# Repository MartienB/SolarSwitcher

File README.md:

The goal of the SolarSwitcher project is to develop a device which can switch between differen power supplies in order to (in this case) power a Raspberry Pi. One of the connected power suppies is a small solar panel and battery, the goal is to use this power source as much as possible, but when the battery runs low, a wallcharger will take over.

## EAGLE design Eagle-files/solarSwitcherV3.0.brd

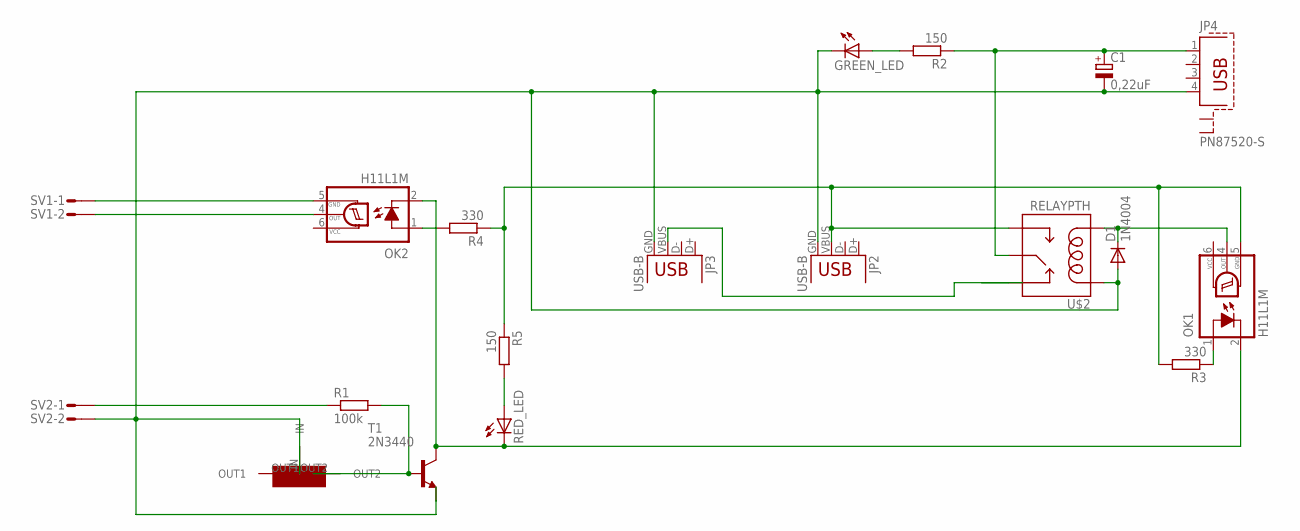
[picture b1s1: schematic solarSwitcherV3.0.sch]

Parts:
C1: 0,22uF; 150CLZ-1014
D1: 1N4004; DO41-10
GREEN_LED: LED5MM
JP2, JP3: USB-B; USB-B-PTH
JP4: PN87520-S
OK1, OK2: H11L1M; DIL06
R1: 100k; 0207/10
R2, R5: 150; 0207/10
R3, R4: 330; 0207/10
RED_LED: LED5MM
SV1, SV2: L02P
T1: 2N3440; TO5
U$2: RELAYPTH; SRD-05VDC-SL-C
U$5: 20k; POT_TRIMMER

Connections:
unnamed: R1.2, T1.2 (B), U$5.OUT2
unnamed: OK2.1 (A), R4.2
unnamed: OK2.4 (OUT), SV1.2
unnamed: R1.1, SV2.1
unnamed: JP3.VBUS, U$2.SWCLOSED (SWCLOSE)
unnamed: OK2.5 (GND), SV1.1
unnamed: C1.+, JP4.1, R2.1, U$2.SWCOMMON
unnamed: OK1.2 (C), OK2.2 (C), RED_LED.K (C), T1.3 (C)
unnamed: JP2.VBUS, OK1.5 (GND), R3.2, R4.1, R5.1, U$2.SWOPEN
unnamed: GREEN_LED.A, R2.2
unnamed: R5.2, RED_LED.A
unnamed: C1.-, D1.A, GREEN_LED.K (C), JP2.GND, JP3.GND, JP4.4, SV2.2, T1.1 (E), U$2.COIL1, U$5.IN
unnamed: D1.C, OK1.4 (OUT), U$2.COIL0
unnamed: OK1.1 (A), R3.1
VCC: OK1.6 (VCC), OK2.6 (VCC)

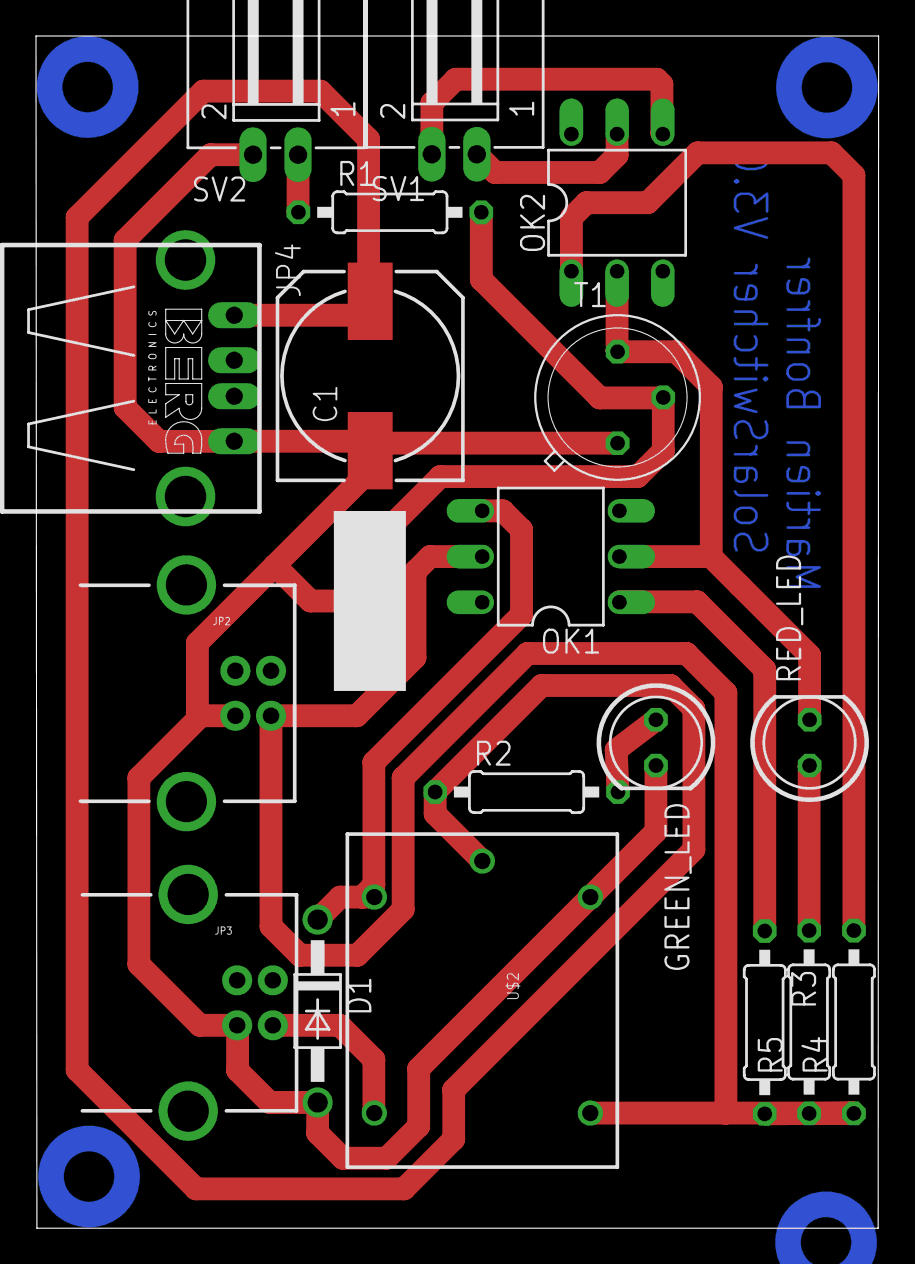
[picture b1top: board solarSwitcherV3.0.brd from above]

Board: 2 copper layers, 46.8 x 66.2 mm, 19 parts (0 on the bottom side), 15 nets.

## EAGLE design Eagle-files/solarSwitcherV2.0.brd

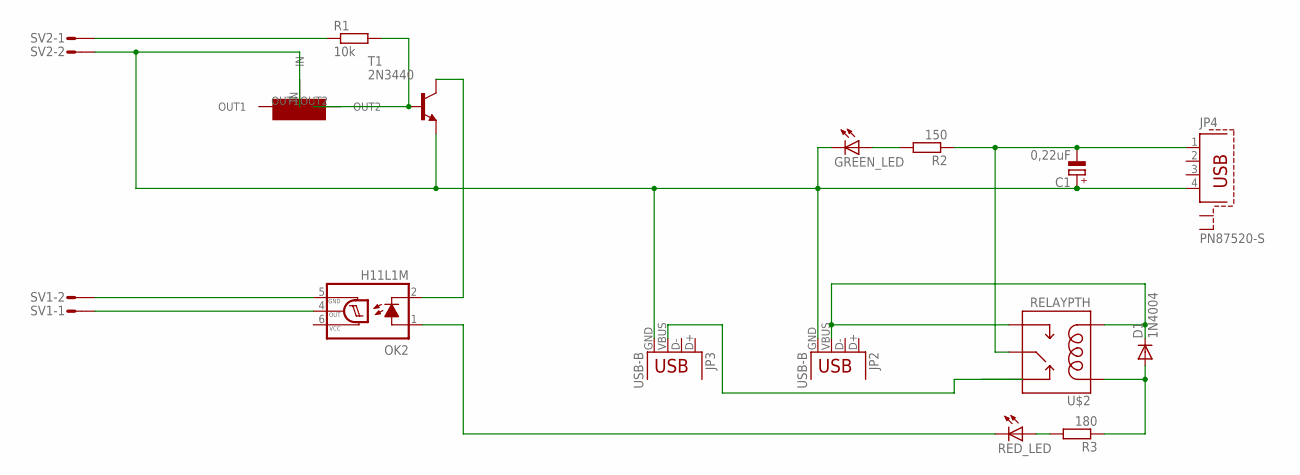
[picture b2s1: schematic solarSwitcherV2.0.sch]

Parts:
C1: 0,22uF; 150CLZ-1014
D1: 1N4004; DO41-10
GREEN_LED: LED5MM
JP2, JP3: USB-B; USB-B-PTH
JP4: PN87520-S
OK2: H11L1M; DIL06
R1: 10k; 0207/10
R2: 150; 0207/10
R3: 180; 0207/10
RED_LED: LED5MM
SV1, SV2: L02P
T1: 2N3440; TO5
U$2: RELAYPTH; SRD-05VDC-SL-C
U$5: 20k; POT_TRIMMER

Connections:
unnamed: R1.2, T1.2 (B), U$5.OUT2
unnamed: C1.-, JP4.1, R2.1, U$2.SWCOMMON
unnamed: OK2.1 (A), RED_LED.K (C)
unnamed: OK2.4 (OUT), SV1.1
unnamed: R1.1, SV2.1
unnamed: JP3.VBUS, U$2.SWCLOSED (SWCLOSE)
unnamed: OK2.5 (GND), SV1.2
unnamed: C1.+, GREEN_LED.K (C), JP2.GND, JP3.GND, JP4.4, SV2.2, T1.1 (E), U$5.IN
unnamed: OK2.2 (C), T1.3 (C)
unnamed: D1.A, R3.1, U$2.COIL1
unnamed: D1.C, JP2.VBUS, U$2.COIL0, U$2.SWOPEN
unnamed: GREEN_LED.A, R2.2
unnamed: R3.2, RED_LED.A
VCC: OK2.6 (VCC)

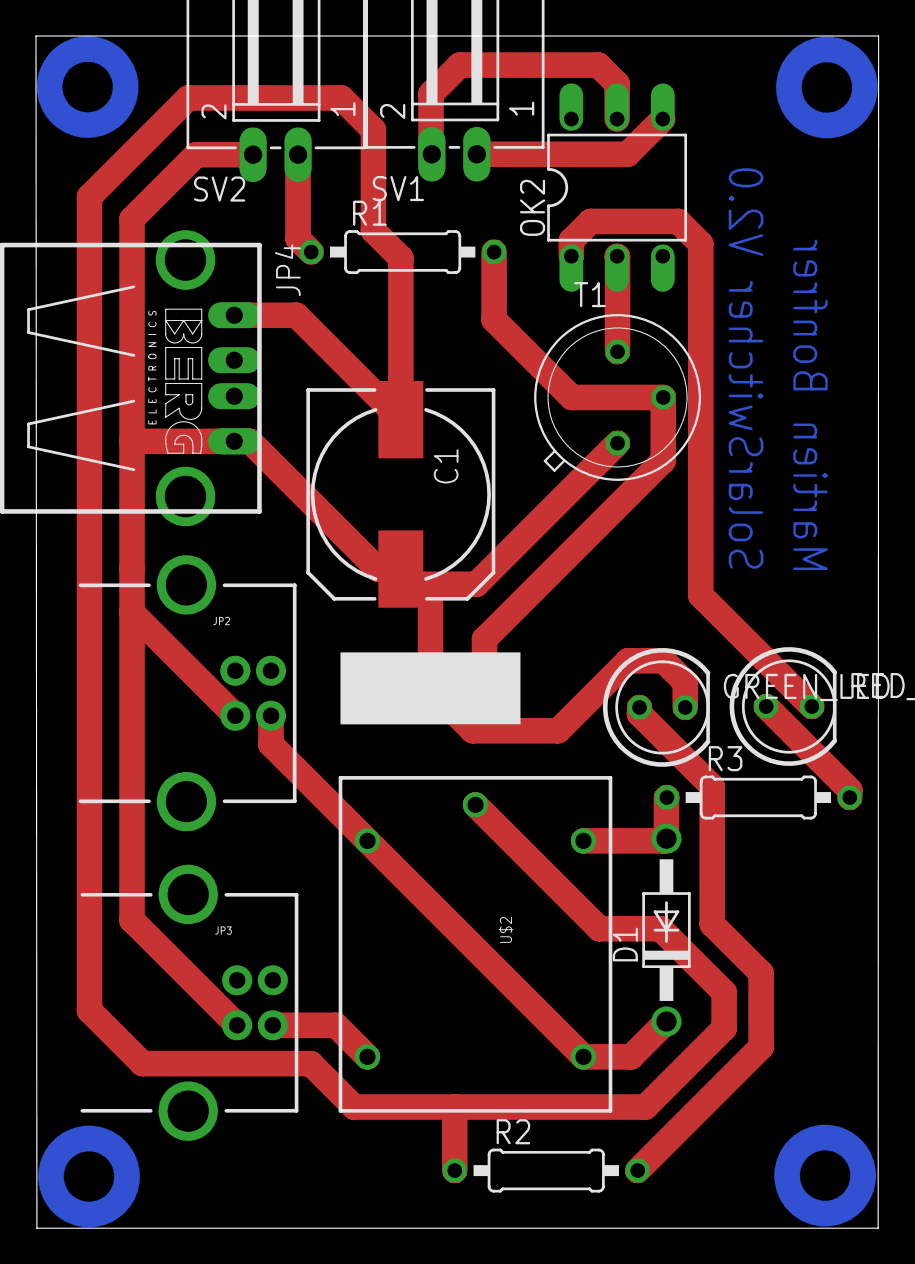
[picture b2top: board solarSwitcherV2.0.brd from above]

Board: 2 copper layers, 46.8 x 66.2 mm, 16 parts (0 on the bottom side), 13 nets.

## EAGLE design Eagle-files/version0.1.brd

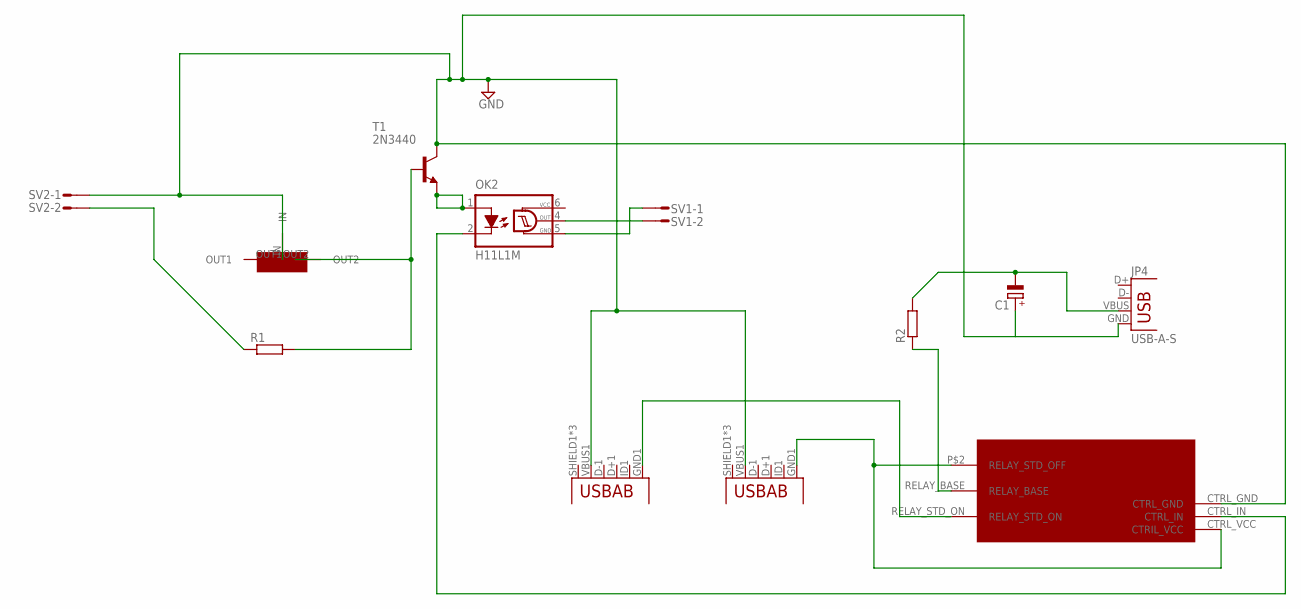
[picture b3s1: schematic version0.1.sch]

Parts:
C1: CPOL-EU150CLZ-1014; 150CLZ-1014
JP2, JP3: USB-ABCONN-11794; USB-AB-MICRO-SMD_V03
JP4: USB-A-S
OK2: H11L1M; DIL06
R1, R2: R-EU_VMTB60; VMTB60
SV1, SV2: L02P
T1: 2N3440; TO5
U$1: RELAY_BOARD
U$5: POT_TRIMMER

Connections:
GND: C1.+, JP2.VBUS1 (VBUS), JP3.VBUS1 (VBUS), JP4.GND, SV2.1, T1.3 (C), U$1.CTRL_GND, U$5.IN
unnamed: R1.2, T1.2 (B), U$5.OUT2
unnamed: C1.-, JP4.VBUS, R2.2
unnamed: OK2.2 (C), U$1.CTRL_IN
unnamed: JP2.GND1 (GND), U$1.CTRL_VCC (CTRIL_VCC), U$1.P$2 (RELAY_STD_OFF)
unnamed: R1.1, SV2.2
unnamed: JP3.GND1 (GND), U$1.RELAY_STD_ON
unnamed: OK2.5 (GND), SV1.1
unnamed: OK2.1 (A), T1.1 (E)
unnamed: OK2.4 (OUT), SV1.2
unnamed: R2.1, U$1.RELAY_BASE
VCC: OK2.6 (VCC)

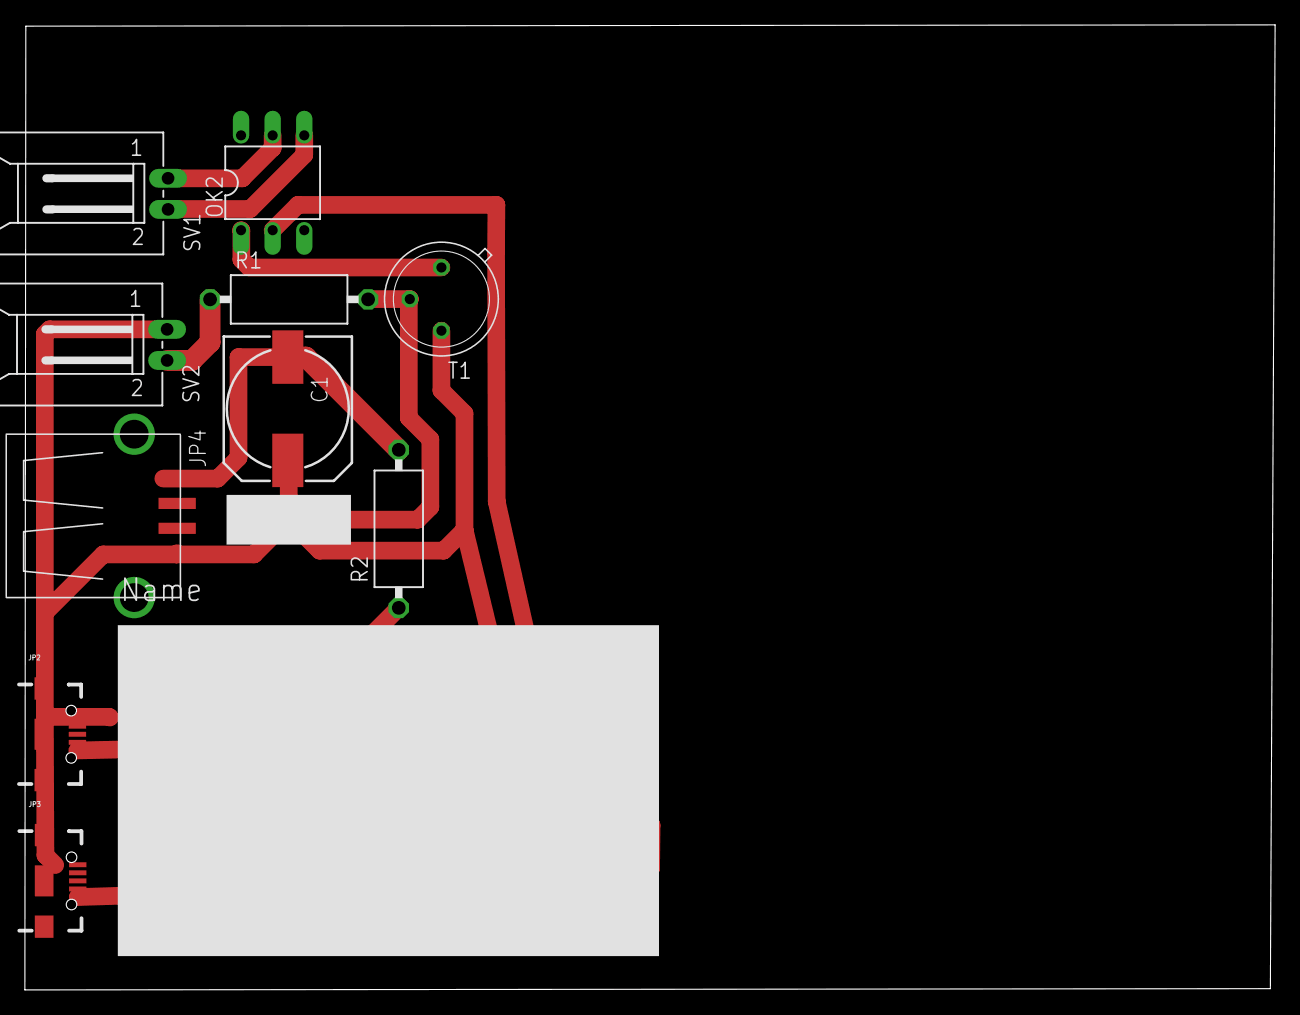
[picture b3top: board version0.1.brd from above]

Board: 2 copper layers, 100.5 x 77.6 mm, 12 parts (0 on the bottom side), 11 nets.

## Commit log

2015-06-09 added custom Eagle Lib files
2015-06-09 Added .gitignor file for Eagle Backup-files
2015-06-09 fixed untracked files
2015-06-09 Added readme file
2015-06-09 renamed ReadMe
2015-06-09 Added images folder
2015-06-10 Started on redesigning the board for ver. 2.0
2015-06-10 Updated .gitignore to remove .epf file
2015-06-10 Removed relay-board and replaced with seperate relay and diode
2015-06-10 Remove non existing files from repo
2015-06-12 Added status leds
2015-06-15 Added missing leds
2015-06-22 Started on version 3.0
2015-06-23 Placed and connected all components

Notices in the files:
parts and their libraries:
SparkFun-Connectors: Licensing: Creative Commons ShareAlike 4.0 International - https://creativecommons.org/licenses/by-sa/4.0
